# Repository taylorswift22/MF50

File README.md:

# MF50
Capacitive replacement PCB for the IBM M50.

This PCB is designed for the M50. Although it shares the F50's matrix and bears similarities to the capacitive PCB from the F50, I think it is unlikely it would function with the F50's original controller and I cannot guarantee it will fit at all.

---

I have tested this in my own M50. I ordered it from JLCPCB with 0.6mm thickness. 

It is designed to be used with the SMD Model F Controller: https://deskthority.net/viewtopic.php?t=24597

I used the "standard" version of the controller, and it fit nicely - but not precisely - in the bottom case.

I do not know if it is compatible with the "4704" version of the controller.

You must have some sort of insulation between the bottom of the PCB and the plate. I cut an insulating layer out a sheet of 0.1mm PVC purchased from here: https://www.amazon.com/dp/B095N7TMZH

**You MUST ground the backplate to the controller** - this is not shown in the image below.

QMK-xwhatsit firmware made by purdeaandrei can be found here: http://35.164.28.200:5000/#/xwhatsit/ibm/f50/universal/LAYOUT

I have not tested this with normal xwhatsit firmware.

---

This project is open source, but I do not endorse it as a starting point for your own Model F PCB project.

Credits:
- purdeaandrei
- dorkvader
- vivilazuli
- theMK

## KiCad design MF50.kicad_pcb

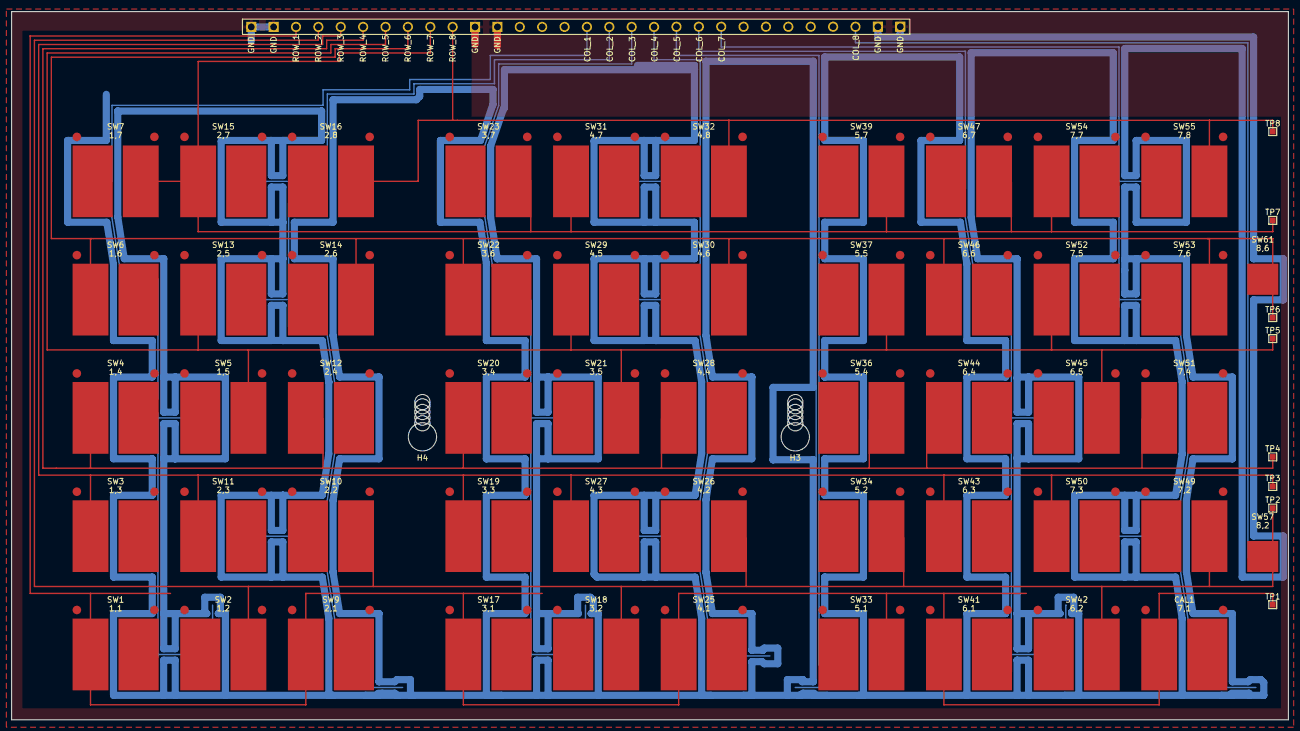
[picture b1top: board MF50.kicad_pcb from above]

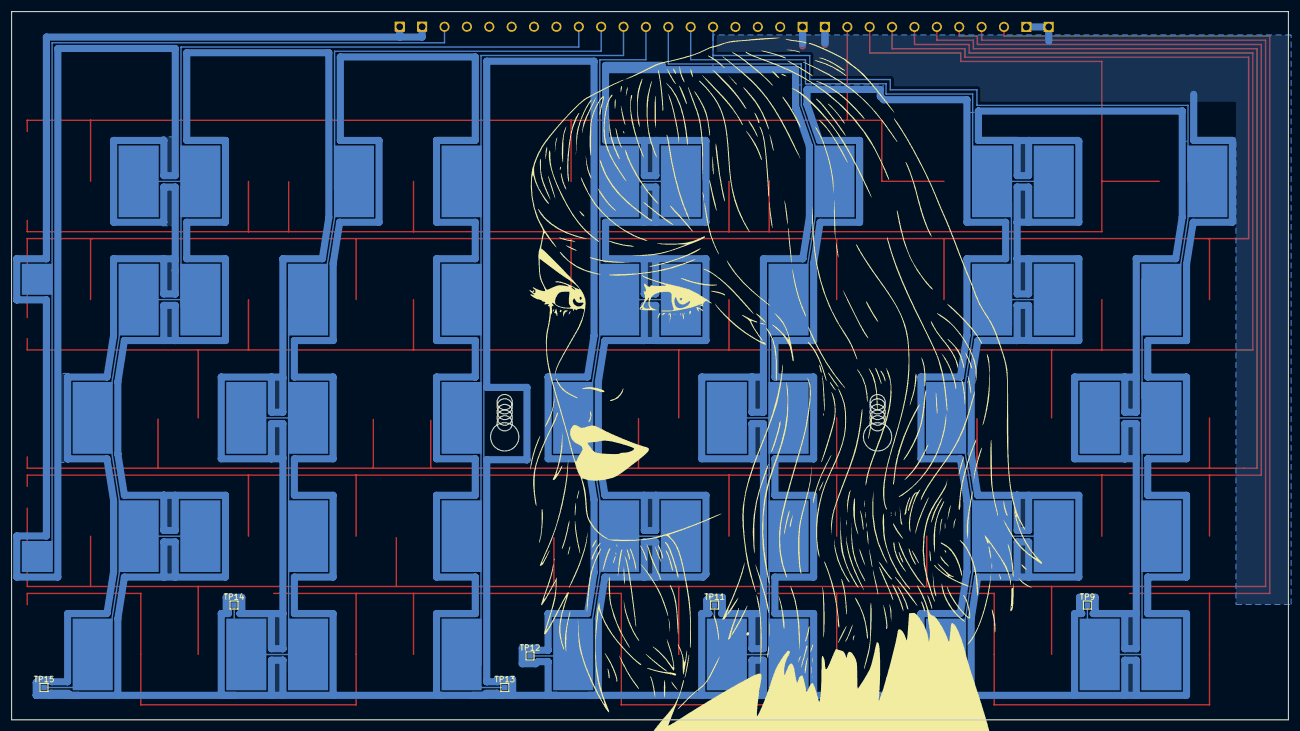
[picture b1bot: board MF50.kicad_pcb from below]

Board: 2 copper layers, 225.9 x 125.3 mm, 70 parts (7 on the bottom side), 17 nets.

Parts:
CAL1: 7,1; SW_CAP_F_R
H3: MountingHole; F50_Hole
H4: XTHole; F50_Hole
J1: CONN_CAP; CONN_CAP_3.96mm
SW1: 1,1; SW_CAP_F_R
SW2: 1,2; SW_CAP_F_L
SW3: 1,3; SW_CAP_F_R
SW4: 1,4; SW_CAP_F_R
SW5: 1,5; SW_CAP_F_L
SW6: 1,6; SW_CAP_F_R
SW7: 1,7; SW_CAP_F_L
SW9: 2,1; SW_CAP_F_R
SW10: 2,2; SW_CAP_F_L
SW11: 2,3; SW_CAP_F_R
SW12: 2,4; SW_CAP_F_R
SW13: 2,5; SW_CAP_F_R
SW14: 2,6; SW_CAP_F_L
SW15: 2,7; SW_CAP_F_R
SW16: 2,8; SW_CAP_F_L
SW17: 3,1; SW_CAP_F_R
SW18: 3,2; SW_CAP_F_L
SW19: 3,3; SW_CAP_F_R
SW20: 3,4; SW_CAP_F_R
SW21: 3,5; SW_CAP_F_L
SW22: 3,6; SW_CAP_F_R
SW23: 3,7; SW_CAP_F_L
SW25: 4,1; SW_CAP_F_R
SW26: 4,2; SW_CAP_F_L
SW27: 4,3; SW_CAP_F_R
SW28: 4,4; SW_CAP_F_R
SW29: 4,5; SW_CAP_F_R
SW30: 4,6; SW_CAP_F_L
SW31: 4,7; SW_CAP_F_R
SW32: 4,8; SW_CAP_F_L
SW33: 5,1; SW_CAP_F_L
SW34: 5,2; SW_CAP_F_L
SW36: 5,4; SW_CAP_F_L
SW37: 5,5; SW_CAP_F_L
SW39: 5,7; SW_CAP_F_L
SW41: 6,1; SW_CAP_F_R
SW42: 6,2; SW_CAP_F_L
SW43: 6,3; SW_CAP_F_R
SW44: 6,4; SW_CAP_F_R
SW45: 6,5; SW_CAP_F_L
SW46: 6,6; SW_CAP_F_R
SW47: 6,7; SW_CAP_F_L
SW49: 7,2; SW_CAP_F_L
SW50: 7,3; SW_CAP_F_R
SW51: 7,4; SW_CAP_F_R
SW52: 7,5; SW_CAP_F_R
SW53: 7,6; SW_CAP_F_L
SW54: 7,7; SW_CAP_F_R
SW55: 7,8; SW_CAP_F_L
SW57: 8,2; CAL_CAP_F
SW61: 8,6; CAL_CAP_F
TP1, TP2, TP3, TP4, TP5, TP6, TP7, TP8, TP9, TP10, TP11, TP12, TP13, TP14, TP15: TestPoint; TestPoint_Pad_1.0x1.0mm

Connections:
COL_1: J1.16 (COL_4), SW1.COL, SW2.COL, SW3.COL, SW4.COL, SW5.COL, SW6.COL, SW7.COL, TP9.1
COL_2: J1.17 (COL_5), SW9.COL, SW10.COL, SW11.COL, SW12.COL, SW13.COL, SW14.COL, SW15.COL, SW16.COL, TP10.1
COL_3: J1.18 (COL_6), SW17.COL, SW18.COL, SW19.COL, SW20.COL, SW21.COL, SW22.COL, SW23.COL, TP11.1
COL_4: J1.19 (COL_7), SW25.COL, SW26.COL, SW27.COL, SW28.COL, SW29.COL, SW30.COL, SW31.COL, SW32.COL, TP12.1
COL_5: J1.20 (COL_8), SW33.COL, SW34.COL, SW36.COL, SW37.COL, SW39.COL, TP13.1
COL_6: J1.21 (COL_9), SW41.COL, SW42.COL, SW43.COL, SW44.COL, SW45.COL, SW46.COL, SW47.COL, TP14.1
COL_7: CAL1.COL, J1.22 (COL_A), SW49.COL, SW50.COL, SW51.COL, SW52.COL, SW53.COL, SW54.COL, SW55.COL, TP15.1
COL_8: J1.28 (COL_G), SW57.COL, SW61.COL
GND: J1.1 (GND), J1.2 (GND), J1.11 (GND), J1.12 (GND), J1.29 (GND), J1.30 (GND)
ROW_1: CAL1.ROW, J1.3 (ROW_1), SW1.ROW, SW9.ROW, SW17.ROW, SW25.ROW, SW33.ROW, SW41.ROW, TP1.1
ROW_2: J1.4 (ROW_2), SW2.ROW, SW10.ROW, SW18.ROW, SW26.ROW, SW34.ROW, SW42.ROW, SW49.ROW, SW57.ROW, TP2.1
ROW_3: J1.5 (ROW_3), SW3.ROW, SW11.ROW, SW19.ROW, SW27.ROW, SW43.ROW, SW50.ROW, TP3.1
ROW_4: J1.6 (ROW_4), SW4.ROW, SW12.ROW, SW20.ROW, SW28.ROW, SW36.ROW, SW44.ROW, SW51.ROW, TP4.1
ROW_5: J1.7 (ROW_5), SW5.ROW, SW13.ROW, SW21.ROW, SW29.ROW, SW37.ROW, SW45.ROW, SW52.ROW, TP5.1
ROW_6: J1.8 (ROW_6), SW6.ROW, SW14.ROW, SW22.ROW, SW30.ROW, SW46.ROW, SW53.ROW, SW61.ROW, TP6.1
ROW_7: J1.9 (ROW_7), SW7.ROW, SW15.ROW, SW23.ROW, SW31.ROW, SW39.ROW, SW47.ROW, SW54.ROW, TP7.1
ROW_8: J1.10 (ROW_8), SW16.ROW, SW32.ROW, SW55.ROW, TP8.1

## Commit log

2023-10-28 Added files.
